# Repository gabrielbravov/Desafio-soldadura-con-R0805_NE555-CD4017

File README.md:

# Desafio-soldadura-con-R0805_NE555-CD4017
Para mejorar la técnica soldando 0805

Se sube a Github en Junio-2023.
PCB creada en Agosto-2022.

TO-DO:
- Agregar pin header a la salida del CD4017. Con esto se pueden probar varias pcb en cascada usando una sola pcb que contenga los IC CD4017 y NE555.
- Cambiar la entrada de energía por USB o por XH2.54, para facilitar la conexión de energía.
- Cambiar el potenciómetro por unas resistencias

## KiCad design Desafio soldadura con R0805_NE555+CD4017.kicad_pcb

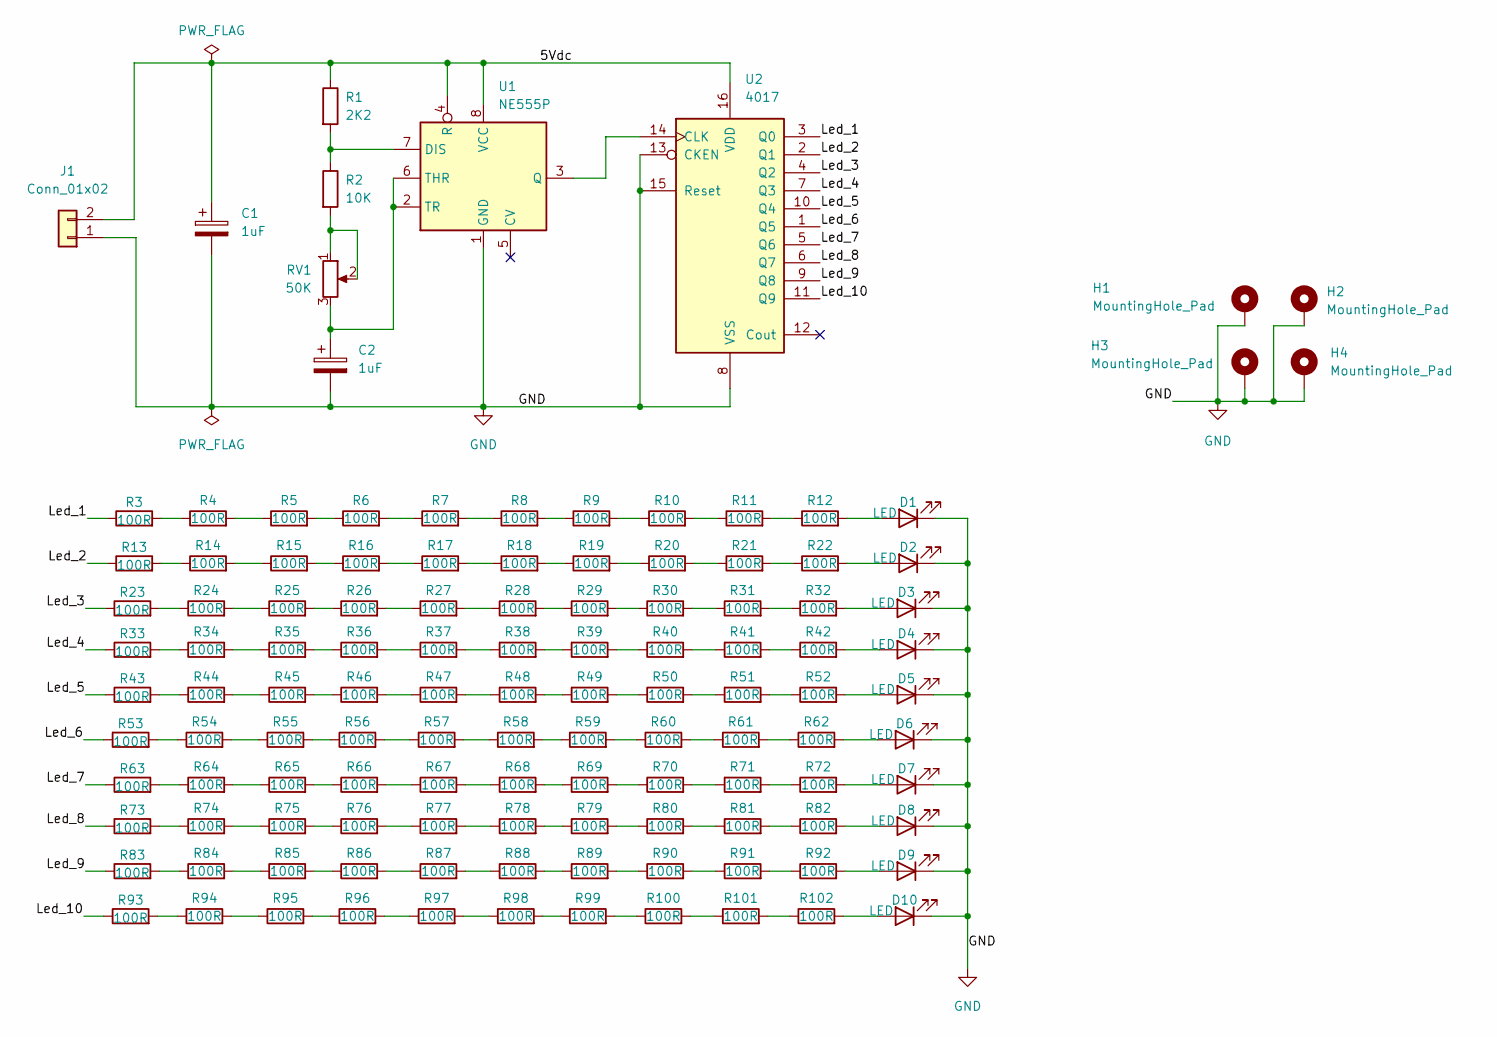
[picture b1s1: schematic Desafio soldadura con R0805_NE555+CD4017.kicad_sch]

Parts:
C1, C2: 1uF; CP_Radial_D4.0mm_P2.00mm
D1, D2, D3, D4, D5, D6, D7, D8, D9, D10: LED; LED_1206_3216Metric_Pad1.42x1.75mm_HandSolder
H1, H2, H3, H4: MountingHole_Pad; MountingHole_2.7mm_M2.5_Pad_Via
J1: Conn_01x02; TestPoint_2Pads_Pitch5.08mm_Drill1.3mm
R1: 2K2; R_Axial_DIN0207_L6.3mm_D2.5mm_P7.62mm_Horizontal
R2: 10K; R_Axial_DIN0207_L6.3mm_D2.5mm_P7.62mm_Horizontal
R3, R4, R5, R6, R7, R8, R9, R10, R11, R12, R13, R14, R15, R16, R17, R18, R19, R20, R21, R22, R23, R24, R25, R26, R27, R28, R29, R30, R31, R32, R33, R34, R35, R36, R37, R38, R39, R40, R41, R42, R43, R44, R45, R46, R47, R48, R49, R50, R51, R52, R53, R54, R55, R56, R57, R58, R59, R60, R61, R62, R63, R64, R65, R66, R67, R68, R69, R70, R71, R72, R73, R74, R75, R76, R77, R78, R79, R80, R81, R82, R83, R84, R85, R86, R87, R88, R89, R90, R91, R92, R93, R94, R95, R96, R97, R98, R99, R100, R101, R102: 100R; R_0805_2012Metric_Pad1.20x1.40mm_HandSolder
RV1: 50K; PinHeader_1x03_P2.54mm_Vertical
U1: NE555P; DIP-8_W7.62mm_Socket
U2: 4017; DIP-16_W7.62mm_Socket_LongPads

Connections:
/5Vdc: C1.1, J1.2, R1.1, U1.4 (R), U1.8 (VCC), U2.16 (VDD)
/Led_1: R3.1, U2.3 (Q0)
/Led_2: R13.1, U2.2 (Q1)
/Led_3: R23.1, U2.4 (Q2)
/Led_4: R33.1, U2.7 (Q3)
/Led_5: R43.1, U2.10 (Q4)
/Led_6: R53.1, U2.1 (Q5)
/Led_7: R63.1, U2.5 (Q6)
/Led_8: R73.1, U2.6 (Q7)
/Led_9: R83.1, U2.9 (Q8)
/Led_10: R93.1, U2.11 (Q9)
GND: C1.2, C2.2, D1.1 (K), D2.1 (K), D3.1 (K), D4.1 (K), D5.1 (K), D6.1 (K), D7.1 (K), D8.1 (K), D9.1 (K), D10.1 (K), H1.1, H2.1, H3.1, H4.1, J1.1, U1.1 (GND), U2.8 (VSS), U2.13 (CKEN), U2.15 (Reset)
unnamed: C2.1, RV1.3, U1.2 (TR), U1.6 (THR)
unnamed: D1.2 (A), R12.2
unnamed: D2.2 (A), R22.2
unnamed: D3.2 (A), R32.2
unnamed: D4.2 (A), R42.2
unnamed: D5.2 (A), R52.2
unnamed: D6.2 (A), R62.2
unnamed: D7.2 (A), R72.2
unnamed: D8.2 (A), R82.2
unnamed: D9.2 (A), R92.2
unnamed: D10.2 (A), R102.2
unnamed: R1.2, R2.1, U1.7 (DIS)
unnamed: R2.2, RV1.1, RV1.2
unnamed: R3.2, R4.1
unnamed: R4.2, R5.1
unnamed: R5.2, R6.1
unnamed: R6.2, R7.1
unnamed: R7.2, R8.1
unnamed: R8.2, R9.1
unnamed: R9.2, R10.1
unnamed: R10.2, R11.1
unnamed: R11.2, R12.1
unnamed: R13.2, R14.1
unnamed: R14.2, R15.1
unnamed: R15.2, R16.1
unnamed: R16.2, R17.1
unnamed: R17.2, R18.1
unnamed: R18.2, R19.1
unnamed: R19.2, R20.1
unnamed: R20.2, R21.1
unnamed: R21.2, R22.1
unnamed: R23.2, R24.1
unnamed: R24.2, R25.1
unnamed: R25.2, R26.1
unnamed: R26.2, R27.1
unnamed: R27.2, R28.1
unnamed: R28.2, R29.1
unnamed: R29.2, R30.1
unnamed: R30.2, R31.1
unnamed: R31.2, R32.1
unnamed: R33.2, R34.1
unnamed: R34.2, R35.1
unnamed: R35.2, R36.1
unnamed: R36.2, R37.1
unnamed: R37.2, R38.1
unnamed: R38.2, R39.1
unnamed: R39.2, R40.1
unnamed: R40.2, R41.1
unnamed: R41.2, R42.1
unnamed: R43.2, R44.1
unnamed: R44.2, R45.1
unnamed: R45.2, R46.1
unnamed: R46.2, R47.1
unnamed: R47.2, R48.1
unnamed: R48.2, R49.1
unnamed: R49.2, R50.1
unnamed: R50.2, R51.1
unnamed: R51.2, R52.1
unnamed: R53.2, R54.1
unnamed: R54.2, R55.1
unnamed: R55.2, R56.1
unnamed: R56.2, R57.1
unnamed: R57.2, R58.1
unnamed: R58.2, R59.1
unnamed: R59.2, R60.1
unnamed: R60.2, R61.1
unnamed: R61.2, R62.1
unnamed: R63.2, R64.1
unnamed: R64.2, R65.1
unnamed: R65.2, R66.1
unnamed: R66.2, R67.1
unnamed: R67.2, R68.1
unnamed: R68.2, R69.1
unnamed: R69.2, R70.1
unnamed: R70.2, R71.1
unnamed: R71.2, R72.1
unnamed: R73.2, R74.1
unnamed: R74.2, R75.1
unnamed: R75.2, R76.1
unnamed: R76.2, R77.1
unnamed: R77.2, R78.1
unnamed: R78.2, R79.1
unnamed: R79.2, R80.1
unnamed: R80.2, R81.1
unnamed: R81.2, R82.1
unnamed: R83.2, R84.1
unnamed: R84.2, R85.1
unnamed: R85.2, R86.1
unnamed: R86.2, R87.1
unnamed: R87.2, R88.1
unnamed: R88.2, R89.1
unnamed: R89.2, R90.1
unnamed: R90.2, R91.1
unnamed: R91.2, R92.1
unnamed: R93.2, R94.1
unnamed: R94.2, R95.1
unnamed: R95.2, R96.1
unnamed: R96.2, R97.1
unnamed: R97.2, R98.1
unnamed: R98.2, R99.1
unnamed: R99.2, R100.1
unnamed: R100.2, R101.1
unnamed: R101.2, R102.1
unnamed: U1.3 (Q), U2.14 (CLK)

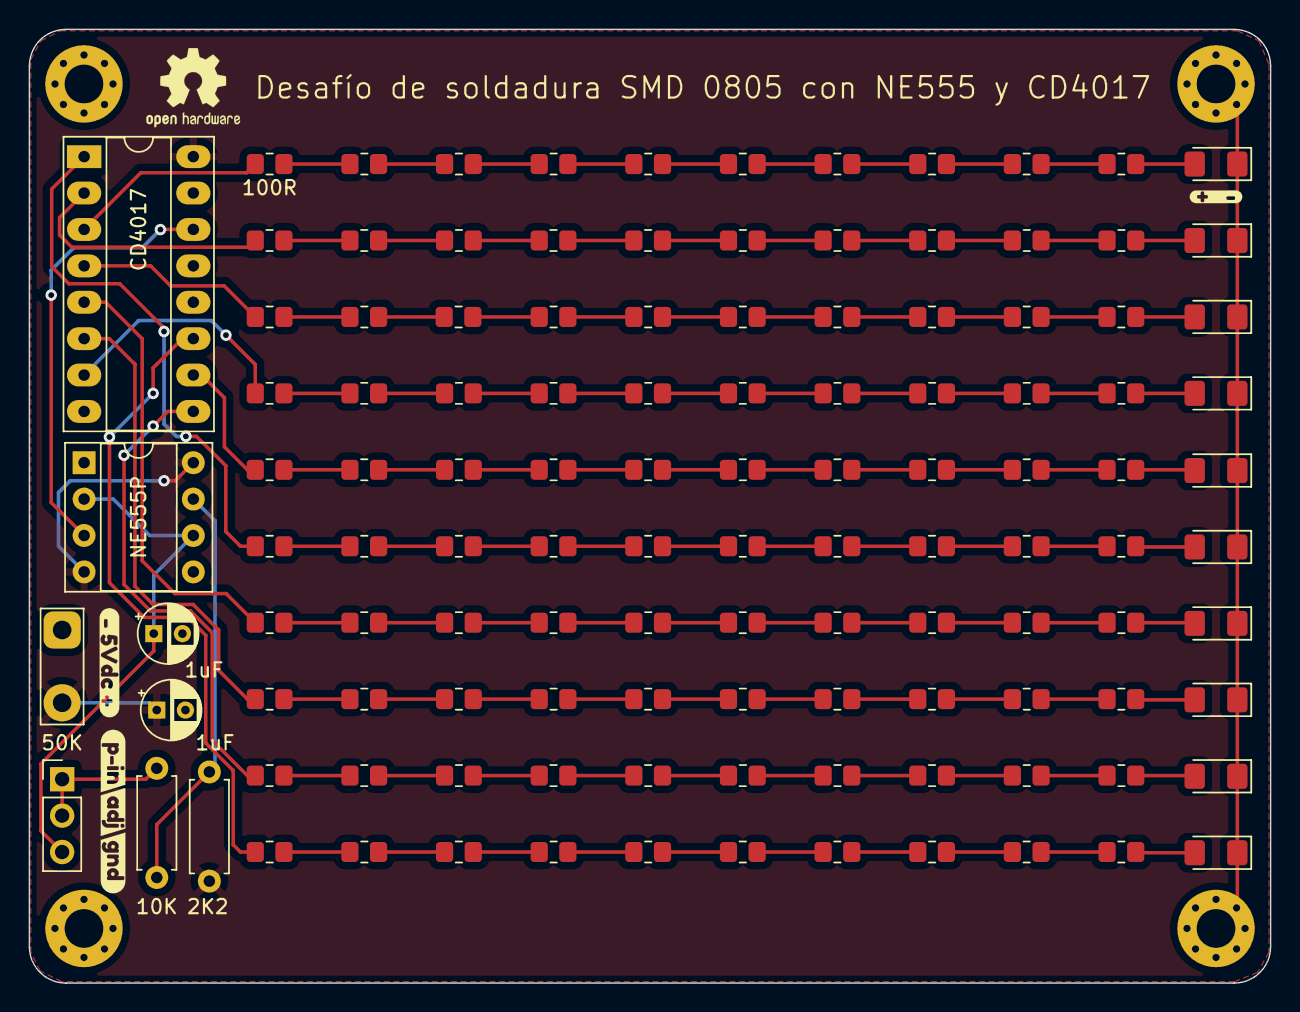
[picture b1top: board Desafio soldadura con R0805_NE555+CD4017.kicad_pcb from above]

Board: 2 copper layers, 86.6 x 66.5 mm, 127 parts (0 on the bottom side), 116 nets.

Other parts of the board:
kibuzzard-62FAA7FD: G***; kibuzzard-62FAA7FD
kibuzzard-62FAAA2E: G***; kibuzzard-62FAAA2E
kibuzzard-62FAAA55: G***; kibuzzard-62FAAA55
kibuzzard-62FAACCE: G***; kibuzzard-62FAACCE
kibuzzard-62FACC93: G***; kibuzzard-62FACC93

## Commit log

2023-06-01 Primer Commit
    Se sube a github para compartir con Comunidad Raptors
    PCB creada en Agosto-2022
2023-06-01 Create Esquematico.pdf
    Se agrega esquemático en pdf para facilitar la visualización del esquemático
